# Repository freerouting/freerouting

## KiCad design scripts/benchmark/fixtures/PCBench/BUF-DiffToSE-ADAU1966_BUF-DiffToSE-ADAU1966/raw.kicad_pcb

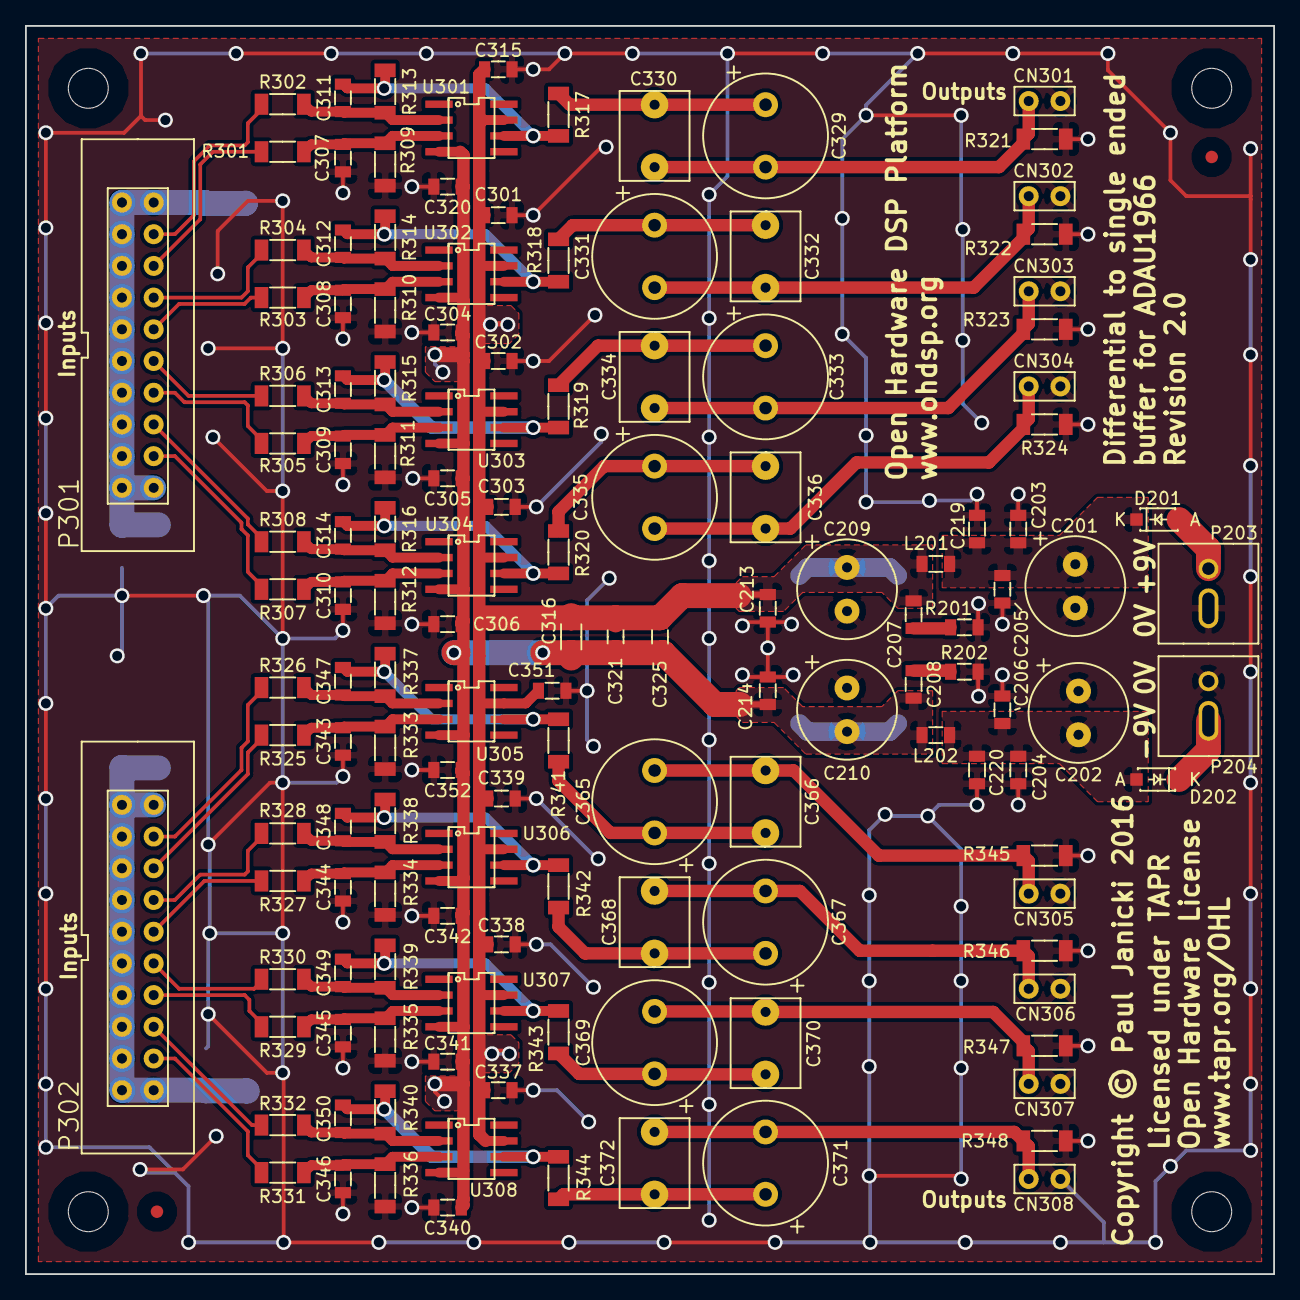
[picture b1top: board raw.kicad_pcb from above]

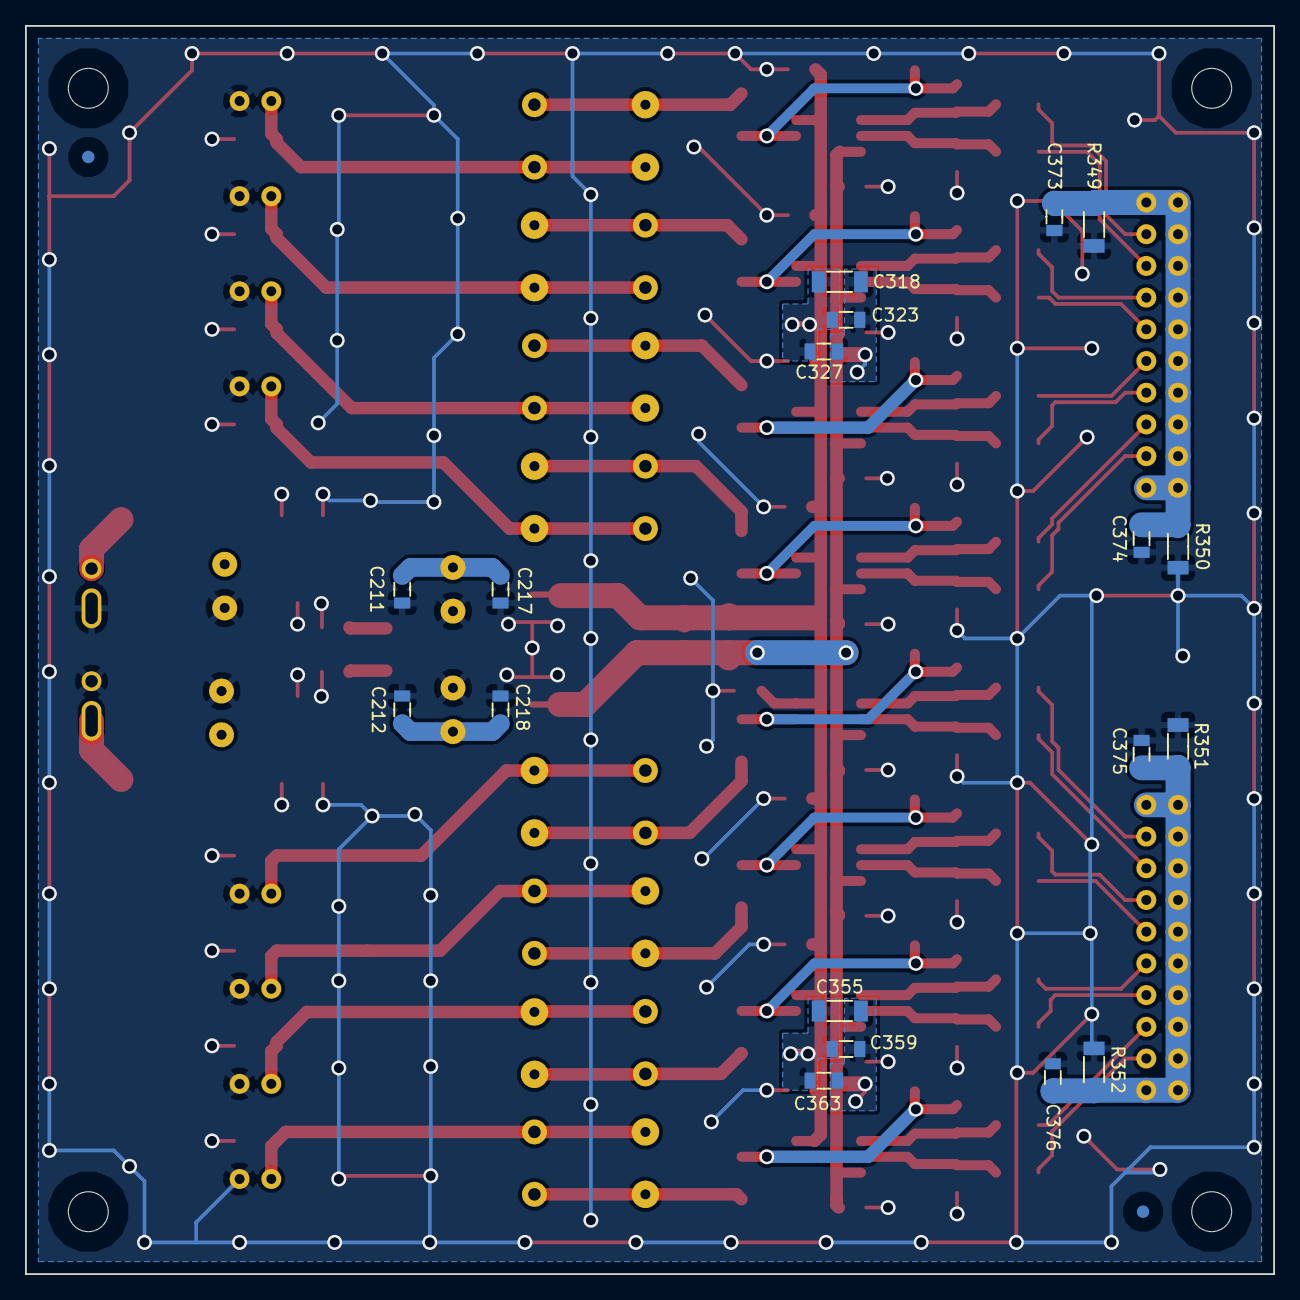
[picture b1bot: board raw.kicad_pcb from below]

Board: 2 copper layers, 100.0 x 100.0 mm, 165 parts (20 on the bottom side), 67 nets.

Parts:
C201, C202, C209, C210: 220u; CAP-TH-D8mmP3.5mm
C203, C204, C211, C212, C301, C302, C303, C304, C305, C306, C315, C320, C321, C323, C337, C338, C339, C340, C341, C342, C351, C352, C359, C373, C374, C375, C376: 100n; SMD-0805
C205, C206, C213, C214, C325, C327, C363: 10n; SMD-0805
C207, C208: 100p; SMD-0805
C217, C218, C219, C220: 22u; SMD-0805
C307, C308, C309, C310, C311, C312, C313, C314, C343, C344, C345, C346, C347, C348, C349, C350: 1n; SMD-0805
C316, C318, C355: 10u; SMD-1206
C329, C331, C333, C335, C365, C367, C369, C371: 100u; CAP-TH-D10mmP5mm
C330, C332, C334, C336, C366, C368, C370, C372: 100n; CAP_TH_5mm
CN301, CN302, CN303, CN304, CN305, CN306, CN307, CN308: COAX; CONN_SIL_2
D201, D202: SS14L; DIODE-SOD-123
FID1, FID2, FID3, FID4: MNT_HOLE; FID-1MM-3MM
L201, L202: 600R@100MHz; SMD-0805
MNT201, MNT202, MNT203, MNT204: MNT_HOLE; MNT_HOLE_3.2mm
P203, P204: CONN_2x1; CONN-2WAY-2.54mm-3.81mm-SPACING
P301, P302: CONN_02X10; CONN_DIL_2X10_BOX
R201, R202: 47; SMD-0805
R301, R302, R303, R304, R305, R306, R307, R308, R325, R326, R327, R328, R329, R330, R331, R332: 1k3; SMD-1206
R309, R310, R311, R312, R313, R314, R315, R316, R333, R334, R335, R336, R337, R338, R339, R340: 1k5; SMD-1206
R317, R318, R319, R320, R341, R342, R343, R344: 100; SMD-1206
R321, R322, R323, R324, R345, R346, R347, R348: 100k; SMD-1206
R349, R350, R351, R352: 10; SMD-1206
U301, U302, U303, U304, U305, U306, U307, U308: TLE2071; IC_SOIC_8

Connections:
+9VA: C207.1, C209.1, C211.1, C213.1, C217.1, C301.1, C302.1, C303.1, C315.1, C316.1, C318.1, C321.1, C323.1, C325.1, C327.1, C337.1, C338.1, C339.1, C351.1, C355.1, C359.1, C363.1, L201.2, U301.7, U302.7, U303.7, U304.7, U305.7, U306.7, U307.7, U308.7
-9VA: C208.2, C210.2, C212.2, C214.2, C218.2, C304.2, C305.2, C306.2, C316.2, C318.2, C320.2, C321.2, C323.2, C325.2, C327.2, C340.2, C341.2, C342.2, C352.2, C355.2, C359.2, C363.2, L202.2, U301.4, U302.4, U303.4, U304.4, U305.4, U306.4, U307.4, U308.4
GNDA: C201.2, C202.1, C203.2, C204.1, C205.2, C206.1, C209.2, C210.1, C211.2, C212.1, C213.2, C214.1, C217.2, C218.1, C219.2, C220.1, C301.2, C302.2, C303.2, C304.1, C305.1, C306.1, C307.2, C308.2, C309.2, C310.2, C315.2, C320.1, C337.2, C338.2, C339.2, C340.1, C341.1, C342.1, C343.2, C344.2, C345.2, C346.2, C351.2, C352.1, C373.2, C374.2, C375.2, C376.2, CN301.2, CN302.2, CN303.2, CN304.2, CN305.2, CN306.2, CN307.2, CN308.2, P203.2, P204.1, R201.2, R202.1, R309.1, R310.1, R311.1, R312.1, R321.1, R322.1, R323.1, R324.1, R333.1, R334.1, R335.1, R336.1, R345.1, R346.1, R347.1, R348.1, R349.1, R350.1, R351.1, R352.1
unnamed: C201.1, C203.1, C205.1, C219.1, D201.2, L201.1
unnamed: C202.2, C204.2, C206.2, C220.2, D202.1, L202.1
unnamed: C207.2, R201.1
unnamed: C208.1, R202.2
unnamed: C307.1, R301.1, R309.2, U301.3
unnamed: C308.1, R303.1, R310.2, U302.3
unnamed: C309.1, R305.1, R311.2, U303.3
unnamed: C310.1, R307.1, R312.2, U304.3
unnamed: C311.1, R302.1, R313.2, U301.2
unnamed: C311.2, R313.1, R317.2, U301.6
unnamed: C312.1, R304.1, R314.2, U302.2
unnamed: C312.2, R314.1, R318.2, U302.6
unnamed: C313.1, R306.1, R315.2, U303.2
unnamed: C313.2, R315.1, R319.2, U303.6
unnamed: C314.1, R308.1, R316.2, U304.2
unnamed: C314.2, R316.1, R320.2, U304.6
unnamed: C329.1, C330.1, R317.1
unnamed: C329.2, C330.2, CN301.1, R321.2
unnamed: C331.1, C332.1, R318.1
unnamed: C331.2, C332.2, CN302.1, R322.2
unnamed: C333.1, C334.1, R319.1
unnamed: C333.2, C334.2, CN303.1, R323.2
unnamed: C335.1, C336.1, R320.1
unnamed: C335.2, C336.2, CN304.1, R324.2
unnamed: C343.1, R325.1, R333.2, U305.3
unnamed: C344.1, R327.1, R334.2, U306.3
unnamed: C345.1, R329.1, R335.2, U307.3
unnamed: C346.1, R331.1, R336.2, U308.3
unnamed: C347.1, R326.1, R337.2, U305.2
unnamed: C347.2, R337.1, R341.2, U305.6
unnamed: C348.1, R328.1, R338.2, U306.2
unnamed: C348.2, R338.1, R342.2, U306.6
unnamed: C349.1, R330.1, R339.2, U307.2
unnamed: C349.2, R339.1, R343.2, U307.6
unnamed: C350.1, R332.1, R340.2, U308.2
unnamed: C350.2, R340.1, R344.2, U308.6
unnamed: C365.1, C366.1, R341.1
unnamed: C365.2, C366.2, CN305.1, R345.2
unnamed: C367.1, C368.1, R342.1
unnamed: C367.2, C368.2, CN306.1, R346.2
unnamed: C369.1, C370.1, R343.1
unnamed: C369.2, C370.2, CN307.1, R347.2
unnamed: C371.1, C372.1, R344.1
unnamed: C371.2, C372.2, CN308.1, R348.2
unnamed: C373.1, C374.1, P301.1, P301.2, P301.3, P301.5, P301.7, P301.9, P301.11, P301.13, P301.15, P301.17, P301.19, P301.20, R349.2, R350.2
unnamed: C375.1, C376.1, P302.1, P302.2, P302.3, P302.5, P302.7, P302.9, P302.11, P302.13, P302.15, P302.17, P302.19, P302.20, R351.2, R352.2
unnamed: D201.1, P203.1
unnamed: D202.2, P204.2
unnamed: P301.4, R302.2
unnamed: P301.6, R301.2
unnamed: P301.8, R304.2
unnamed: P301.10, R303.2
unnamed: P301.12, R306.2
unnamed: P301.14, R305.2
unnamed: P301.16, R308.2
unnamed: P301.18, R307.2
unnamed: P302.4, R326.2
unnamed: P302.6, R325.2
unnamed: P302.8, R328.2
unnamed: P302.10, R327.2
unnamed: P302.12, R330.2
unnamed: P302.14, R329.2
unnamed: P302.16, R332.2
unnamed: P302.18, R331.2

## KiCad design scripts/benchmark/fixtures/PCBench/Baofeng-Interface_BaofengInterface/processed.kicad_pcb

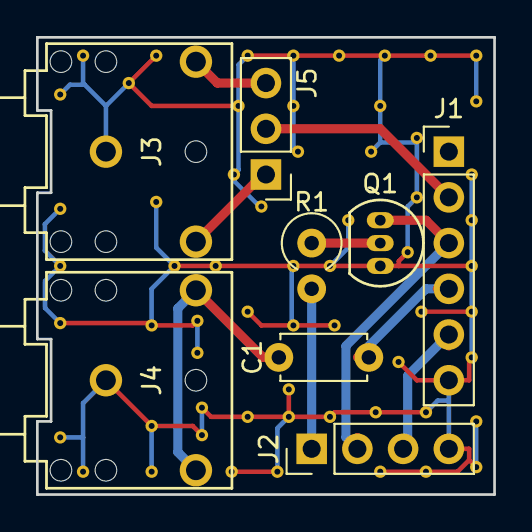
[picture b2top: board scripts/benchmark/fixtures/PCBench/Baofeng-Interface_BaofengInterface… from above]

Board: 2 copper layers, 25.4 x 25.4 mm, 8 parts (0 on the bottom side), 10 nets.

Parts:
C1: 1uF; C_Disc_D4.7mm_W2.5mm_P5.00mm
J1: CONN_01X06; Pin_Header_Straight_1x06_Pitch2.54mm
J2: CONN_01X04; Pin_Header_Straight_1x04_Pitch2.54mm
J3, J4: JACK_TRS_3PINS; SJ1-352XN
J5: CONN_01X03; Pin_Header_Straight_1x03_Pitch2.54mm
Q1: Q_NPN_CBE; TO-92_Inline_Narrow_Oval
R1: 1k; R_Axial_DIN0309_L9.0mm_D3.2mm_P2.54mm_Vertical

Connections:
GND: J1.6, J2.4, J3.1, J4.1, Q1.3
unnamed: C1.1, J4.2, J4.3
unnamed: Q1.2, R1.1
PTT: J2.1, R1.2
RX_AUDIO: C1.2, J1.4
SERIAL_RX: J1.3, J2.2, Q1.1
SERIAL_TX: J1.5, J2.3
TX_AUDIO: J1.2, J5.2
TX_LEFT+: J3.3, J5.3
TX_RIGHT+: J3.2, J5.1

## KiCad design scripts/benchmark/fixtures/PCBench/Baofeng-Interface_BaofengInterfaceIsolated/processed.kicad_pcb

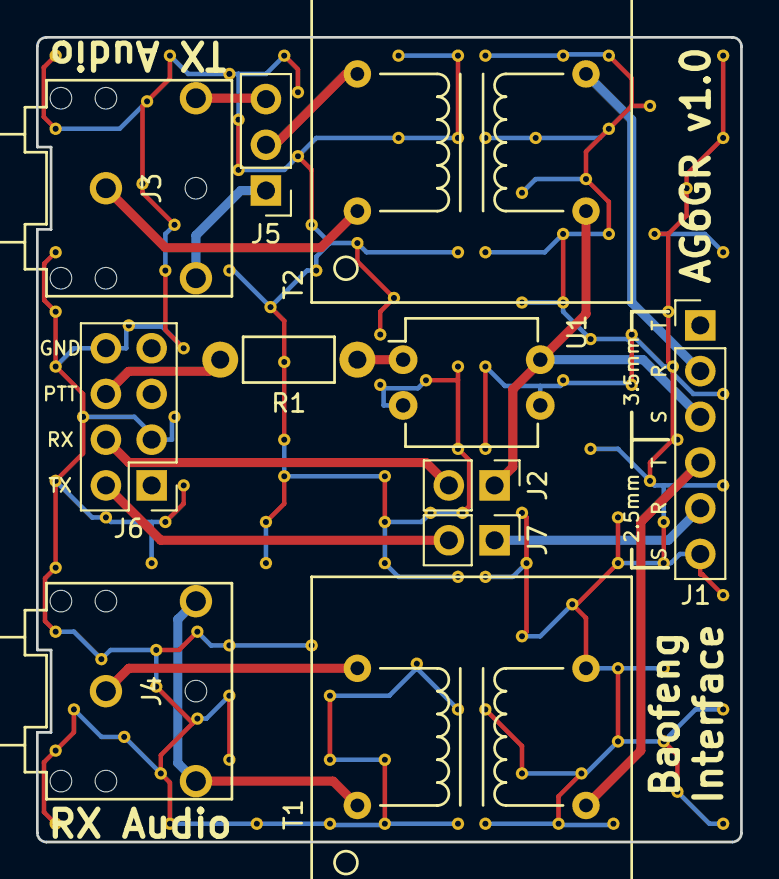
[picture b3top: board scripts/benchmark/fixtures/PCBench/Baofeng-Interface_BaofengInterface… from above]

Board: 2 copper layers, 39.1 x 44.7 mm, 11 parts (0 on the bottom side), 16 nets.

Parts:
J1: CONN_01X06; Pin_Header_Straight_1x06_Pitch2.54mm
J2, J7: CONN_01X02; Pin_Header_Straight_1x02_Pitch2.54mm
J3, J4: JACK_TRS_3PINS; SJ1-352XN
J5: CONN_01X03; Pin_Header_Straight_1x03_Pitch2.54mm
J6: CONN_02X04; Pin_Header_Straight_2x04_Pitch2.54mm
R1: 100; Resistor_Horizontal_RM7mm
T1, T2: LM-NP-1001-B1L; LM-LP-1001L
U1: LTV-817; DIP-4_W7.62mm

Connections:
GND: J6.3, J6.8, U1.2
GNDA: J1.6, T1.5, U1.3
unnamed: J1.5, J7.1
unnamed: J3.1, T2.1
unnamed: J4.1, T1.4
unnamed: J4.2, J4.3, T1.1
unnamed: J5.2, T2.4
unnamed: R1.1, U1.1
PTT_B: J6.6, R1.2
RX_AUDIO: J1.4, T1.8
SERIAL_RX: J2.2, J6.4
SERIAL_TX: J6.2, J7.2
TX_AUDIO+: J1.2, T2.5
TX_AUDIO-: J1.3, J2.1, T2.8, U1.4
TX_LEFT+: J3.3, J5.3
TX_RIGHT+: J3.2, J5.1

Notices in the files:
scripts/benchmark/fixtures/PCBench/BUF-DiffToSE-ADAU1966_BUF-DiffToSE-ADAU1966/raw.kicad_pcb:
Licensed under the TAPR Open Hardware License (www.tapr.org/OHL). This documentation
Copyright Paul Janicki 2016
Copyright © Paul Janicki 2016
Licensed under TAPR
